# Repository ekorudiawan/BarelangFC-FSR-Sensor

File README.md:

# BarelangFC-FSR-Sensor
BarelangFC-FSR-Sensor

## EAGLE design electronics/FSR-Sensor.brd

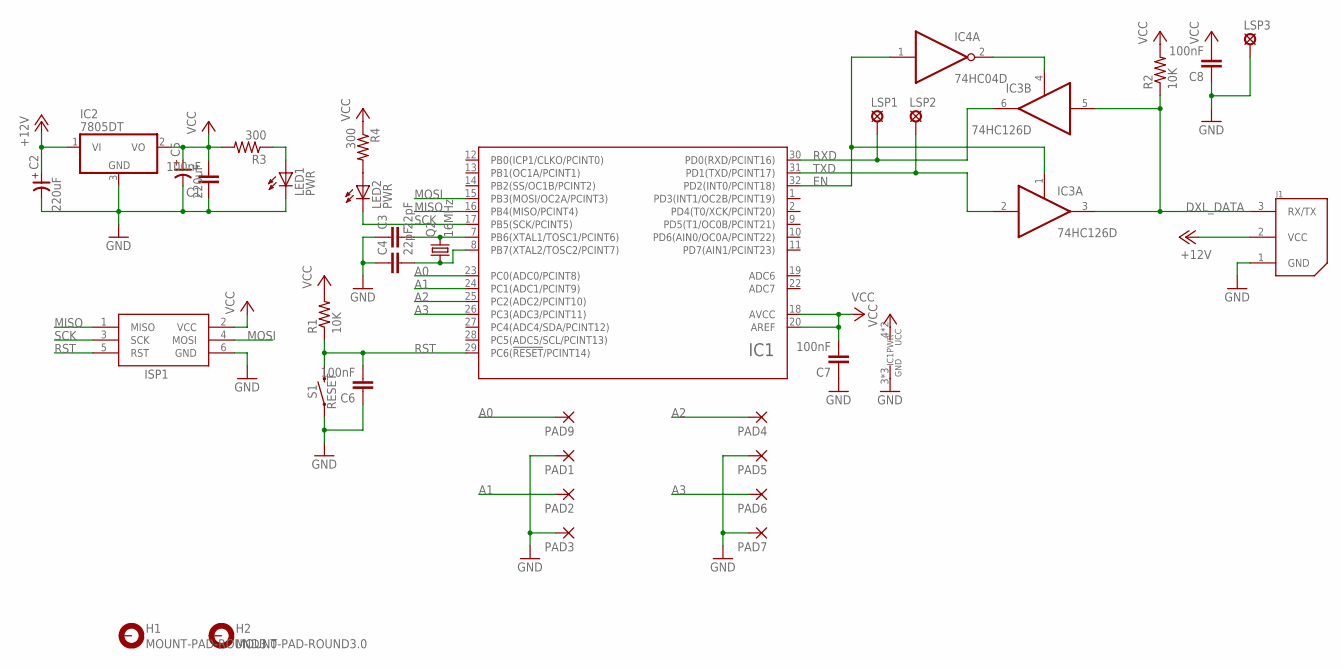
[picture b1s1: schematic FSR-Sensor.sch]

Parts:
C1, C6, C7, C8: 100nF; C0805K
C2, C5: 220uF; 7343/T
C3, C4: 22pF; C0805K
H1, H2: MOUNT-PAD-ROUND3.0; 3,0-PAD
IC1: ATMEGA48/88/168/328-AU; TQFP32-08
IC2: 7805DT; TO252
IC3: 74HC126D; SO14
IC4: 74HC04D; SO14
ISP1: AVRISP-6; AVRISP
J1: 22-03-5035; 5267-3
LED1, LED2: PWR; CHIP-LED0805
LSP1, LSP2, LSP3: LSP10
PAD1, PAD2, PAD3, PAD4, PAD5, PAD6, PAD7, PAD9: SMD2; SMD1,27-2,54
Q2: 16MHz; HC49UP
R1, R2: 10K; R0805
R3, R4: 300; R0805
S1: RESET; TACTILE_SWITCH_SMD_6.0X3.5MM

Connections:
+12V: C2.+, IC2.1 (VI), J1.2 (VCC)
A0: IC1.23 (PC0(ADC0/PCINT8)), PAD9.1
A1: IC1.24 (PC1(ADC1/PCINT9)), PAD2.1
A2: IC1.25 (PC2(ADC2/PCINT10)), PAD4.1
A3: IC1.26 (PC3(ADC3/PCINT11)), PAD6.1
DXL_DATA: IC3.3 (O), IC3.5 (I), J1.3 (RX/TX), R2.1
EN: IC1.32 (PD2(INT0/PCINT18)), IC3.1 (OE), IC4.1 (I)
GND: C1.1, C2.-, C3.1, C4.1, C5.-, C6.1, C7.1, C8.1, IC1.3 (GND), IC1.5 (GND), IC1.21 (GND), IC2.3 (GND), IC3.7 (GND), IC4.7 (GND), ISP1.6 (GND), J1.1 (GND), LED1.C, LSP3.MP, PAD1.1, PAD3.1, PAD5.1, PAD7.1, S1.1
MISO: IC1.16 (PB4(MISO/PCINT4)), ISP1.1 (MISO)
MOSI: IC1.15 (PB3(MOSI/OC2A/PCINT3)), ISP1.4 (MOSI)
unnamed: C3.2, IC1.7 (PB6(XTAL1/TOSC1/PCINT6)), Q2.2
unnamed: C4.2, IC1.8 (PB7(XTAL2/TOSC2/PCINT7)), Q2.1
unnamed: LED1.A, R3.1
unnamed: LED2.A, R4.2
unnamed: IC3.4 (OE), IC4.2 (O)
RST: C6.2, IC1.29 (PC6(!RESET!/PCINT14)), ISP1.5 (RST), R1.1, S1.2
RXD: IC1.30 (PD0(RXD/PCINT16)), IC3.6 (O), LSP1.MP
SCK: IC1.17 (PB5(SCK/PCINT5)), ISP1.3 (SCK), LED2.C
TXD: IC1.31 (PD1(TXD/PCINT17)), IC3.2 (I), LSP2.MP
VCC: C1.2, C5.+, C7.2, C8.2, IC1.4 (UCC), IC1.6 (UCC), IC1.18 (AVCC), IC1.20 (AREF), IC2.2 (VO), IC3.14 (VCC), IC4.14 (VCC), ISP1.2 (VCC), R1.2, R2.2, R3.2, R4.1

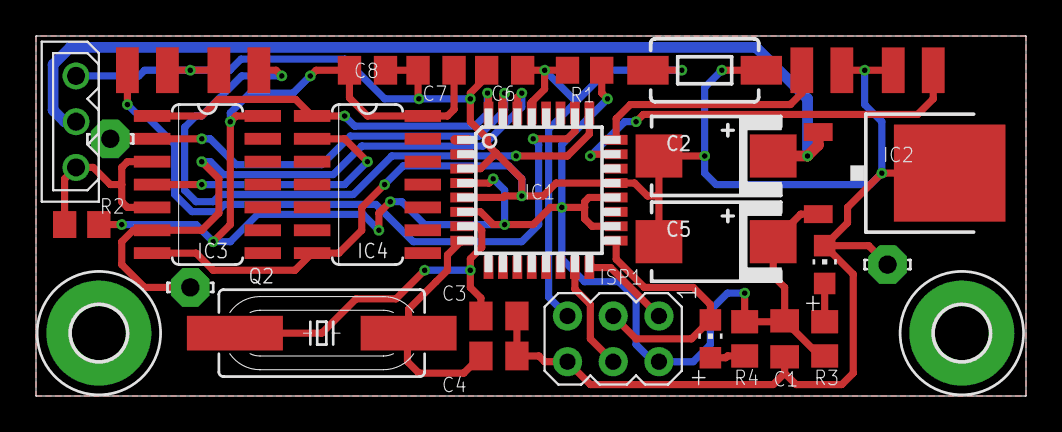
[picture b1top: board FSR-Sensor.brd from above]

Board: 2 copper layers, 55.0 x 20.0 mm, 35 parts (0 on the bottom side), 20 nets.

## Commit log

2019-10-08 Added electronics design files

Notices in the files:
parts and their libraries:
SparkFun-Switches: Licensing: Creative Commons ShareAlike 4.0 International - https://creativecommons.org/licenses/by-sa/4.0
